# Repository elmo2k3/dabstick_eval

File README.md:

# DABStick Eval - Experimental board for SI4688 FM/DAB+ receiver with STM32F4 and audio codec

![Image of DABPStick Eval v1 PCB]
(https://github.com/elmo2k3/dabstick_eval/blob/master/pics/dabstick_v1.jpg)

## Warning

This project is still work in progress

## Hardware

* STM32F427VIT6 microcontroller
  * 2MB Flash, 256KB SRAM
  * Up to 180MHz, here 168MHz
* SI4688-A10-GM FM / HD / DAB / DAB + radio receiver
* CS43L22 Audio DAC with integrated class D speaker driver
* General purpose 2x40 pin headers
* Power by USB or screw connector

## Functional overview

![Graph of functional overview]
(https://github.com/elmo2k3/dabstick_eval/blob/master/doc/DABStick_overview.png)

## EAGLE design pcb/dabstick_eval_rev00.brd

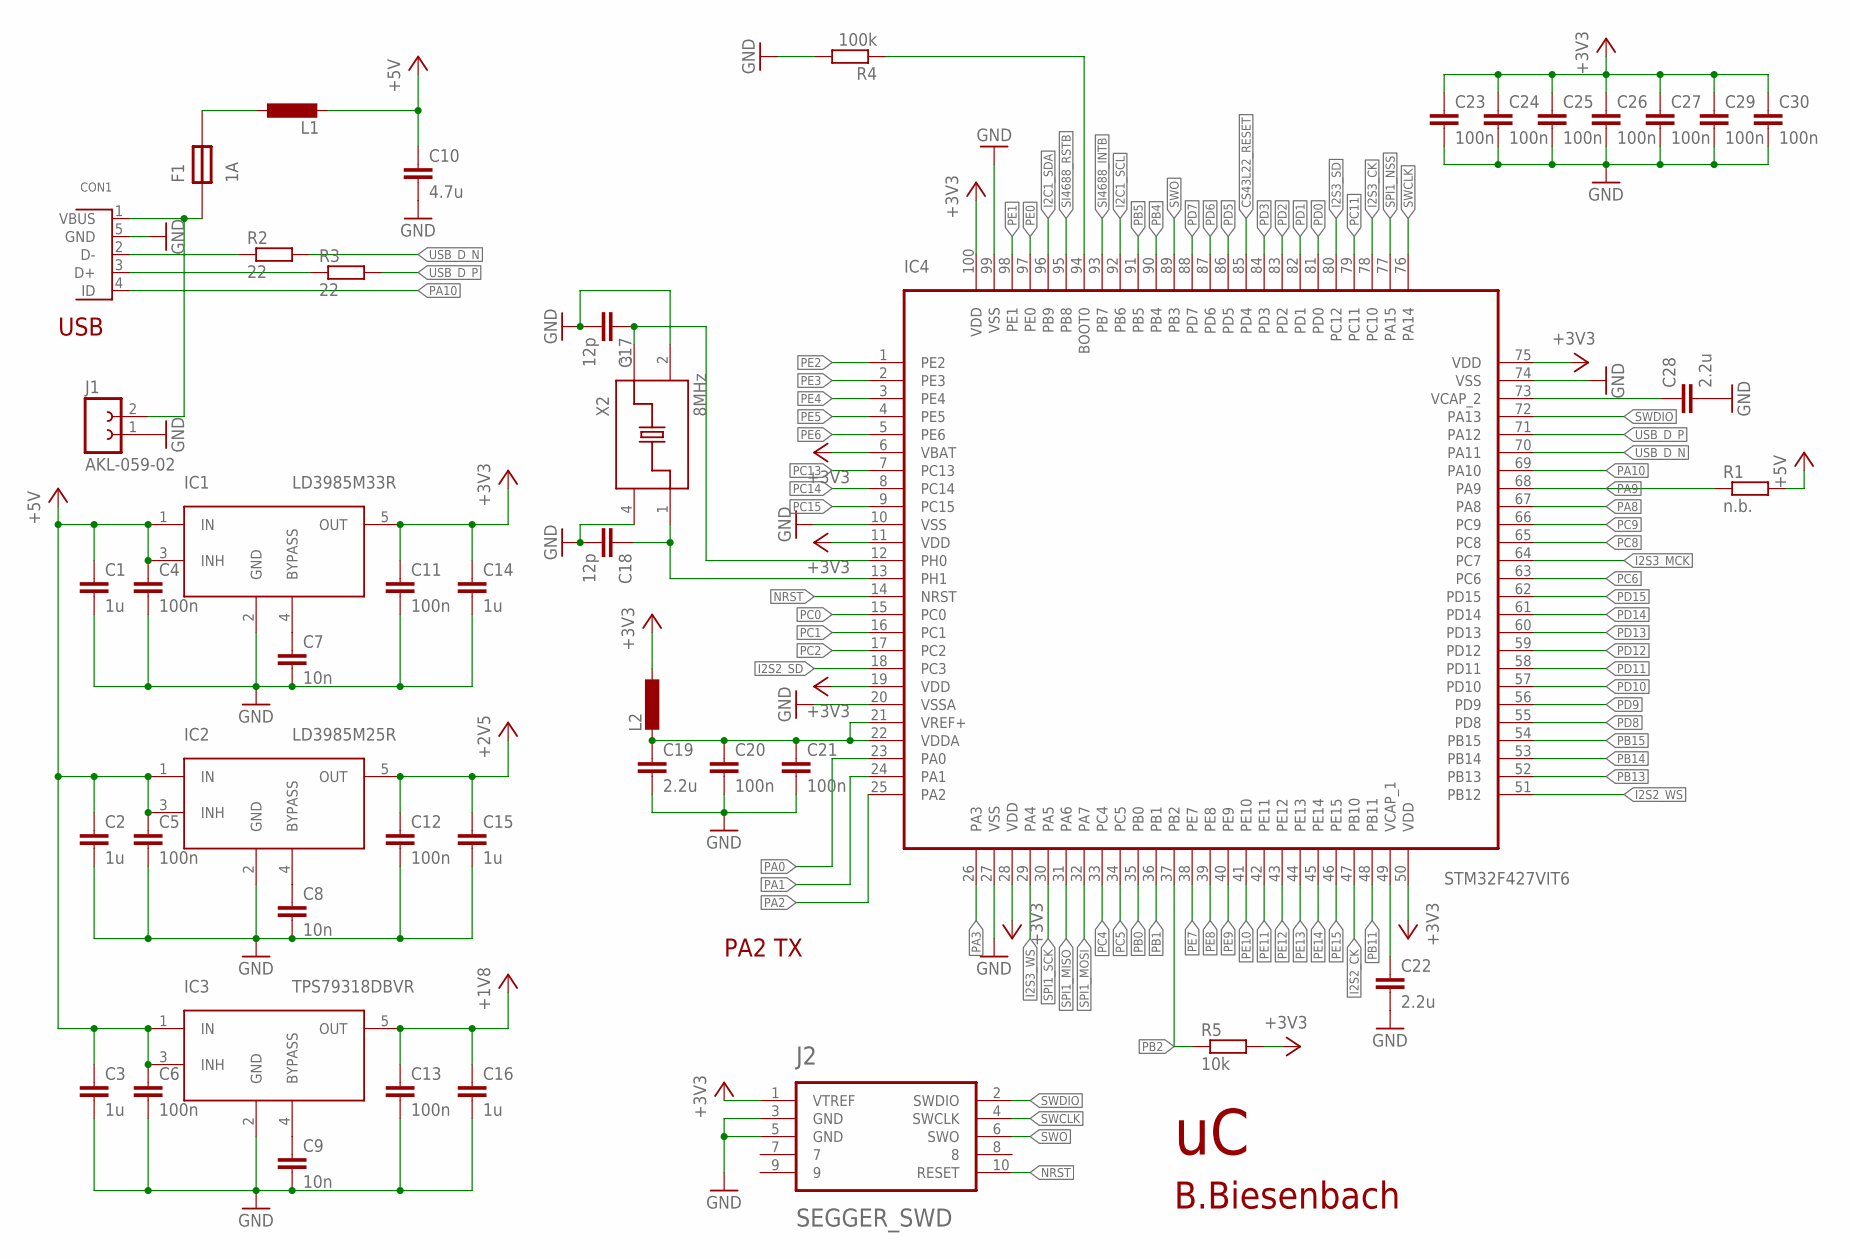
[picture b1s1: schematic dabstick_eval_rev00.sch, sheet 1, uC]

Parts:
C1, C2, C3, C14, C15, C16: 1u; SMD0603
C4, C5, C6, C11, C12, C13, C20, C21, C23, C24, C25, C26, C27, C29, C30: 100n; SMD0603
C7, C8, C9: 10n; SMD0603
C10: 4.7u; 0805
C17, C18: 12p; SMD0603
C19, C22, C28: 2.2u; SMD0603
CON1: USB; USB-B-MICRO-SMT
F1: 1A; SMD_FUSE
IC1: LD3985M33R; SOT23-5
IC2: LD3985M25R; SOT23-5
IC3: TPS79318DBVR; SOT23-5
IC4: STM32F427VIT6; LQFP100
J1: AKL-059-02
J2: SEGGER_SWD; HEADER_10_1.27
L1: L08050805; 0805
L2: L0603; SMD0603
R1: n.b.; SMD0603
R2, R3: 22; SMD0603
R4: 100k; SMD0603
R5: 10k; SMD0603
X2: 8MHz; XTAL_3.2X5

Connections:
+1V8: C13.1, C16.1, IC3.5 (OUT); also elsewhere on the board
+2V5: C12.1, C15.1, IC2.5 (OUT); also elsewhere on the board
+3V3: C11.1, C14.1, C23.1, C24.1, C25.1, C26.1, C27.1, C29.1, C30.1, IC1.5 (OUT), IC4.6 (VBAT), IC4.11 (VDD), IC4.19 (VDD), IC4.28 (VDD), IC4.50 (VDD), IC4.75 (VDD), IC4.100 (VDD), J2.1 (VTREF), L2.1, R5.2; also elsewhere on the board
+5V: C1.1, C2.1, C3.1, C4.1, C5.1, C6.1, C10.1, IC1.1 (IN), IC1.3 (INH), IC2.1 (IN), IC2.3 (INH), IC3.1 (IN), IC3.3 (INH), L1.2, R1.2; also elsewhere on the board
CS43L22_RESET: IC4.85 (PD4); also elsewhere on the board
GND: C1.2, C2.2, C3.2, C4.2, C5.2, C6.2, C7.2, C8.2, C9.2, C10.2, C11.2, C12.2, C13.2, C14.2, C15.2, C16.2, C17.2, C18.2, C19.2, C20.2, C21.2, C22.2, C23.2, C24.2, C25.2, C26.2, C27.2, C28.2, C29.2, C30.2, CON1.5 (GND), IC1.2 (GND), IC2.2 (GND), IC3.2 (GND), IC4.10 (VSS), IC4.20 (VSSA), IC4.27 (VSS), IC4.74 (VSS), IC4.99 (VSS), J1.1, J2.3 (GND), J2.5 (GND), R4.2, X2.2 (GND), X2.4 (GND); also elsewhere on the board
I2C1_SCL: IC4.92 (PB6); also elsewhere on the board
I2C1_SDA: IC4.96 (PB9); also elsewhere on the board
I2S2_CK: IC4.47 (PB10); also elsewhere on the board
I2S2_SD: IC4.18 (PC3); also elsewhere on the board
I2S2_WS: IC4.51 (PB12); also elsewhere on the board
I2S3_CK: IC4.78 (PC10); also elsewhere on the board
I2S3_MCK: IC4.64 (PC7); also elsewhere on the board
I2S3_SD: IC4.80 (PC12); also elsewhere on the board
I2S3_WS: IC4.29 (PA4); also elsewhere on the board
unnamed: C7.1, IC1.4 (BYPASS)
unnamed: C8.1, IC2.4 (BYPASS)
unnamed: C9.1, IC3.4 (BYPASS)
unnamed: C19.1, C20.1, C21.1, IC4.21 (VREF+), IC4.22 (VDDA), L2.2
unnamed: C28.1, IC4.73 (VCAP_2)
unnamed: C22.1, IC4.49 (VCAP_1)
unnamed: CON1.3 (D+), R3.1
unnamed: CON1.2 (D-), R2.1
unnamed: C18.1, IC4.13 (PH1), X2.1
unnamed: C17.1, IC4.12 (PH0), X2.3
unnamed: IC4.94 (BOOT0), R4.1
unnamed: F1.P$2, L1.1
unnamed: CON1.1 (VBUS), F1.P$1, J1.2
NRST: IC4.14 (NRST), J2.10 (RESET); also elsewhere on the board
PA0: IC4.23 (PA0); also elsewhere on the board
PA1: IC4.24 (PA1); also elsewhere on the board
PA2: IC4.25 (PA2); also elsewhere on the board
PA3: IC4.26 (PA3); also elsewhere on the board
PA8: IC4.67 (PA8); also elsewhere on the board
PA9: IC4.68 (PA9), R1.1; also elsewhere on the board
PA10: CON1.4 (ID), IC4.69 (PA10); also elsewhere on the board
PB0: IC4.35 (PB0); also elsewhere on the board
PB1: IC4.36 (PB1); also elsewhere on the board
PB2: IC4.37 (PB2), R5.1; also elsewhere on the board
PB4: IC4.90 (PB4); also elsewhere on the board
PB5: IC4.91 (PB5); also elsewhere on the board
PB11: IC4.48 (PB11); also elsewhere on the board
PB13: IC4.52 (PB13); also elsewhere on the board
PB14: IC4.53 (PB14); also elsewhere on the board
PB15: IC4.54 (PB15); also elsewhere on the board
PC0: IC4.15 (PC0); also elsewhere on the board
PC1: IC4.16 (PC1); also elsewhere on the board
PC2: IC4.17 (PC2); also elsewhere on the board
PC4: IC4.33 (PC4); also elsewhere on the board
PC5: IC4.34 (PC5); also elsewhere on the board
PC6: IC4.63 (PC6); also elsewhere on the board
PC8: IC4.65 (PC8); also elsewhere on the board
PC9: IC4.66 (PC9); also elsewhere on the board
PC11: IC4.79 (PC11); also elsewhere on the board
PC13: IC4.7 (PC13); also elsewhere on the board
PC14: IC4.8 (PC14); also elsewhere on the board
PC15: IC4.9 (PC15); also elsewhere on the board
PD0: IC4.81 (PD0); also elsewhere on the board
PD1: IC4.82 (PD1); also elsewhere on the board
PD2: IC4.83 (PD2); also elsewhere on the board
PD3: IC4.84 (PD3); also elsewhere on the board
PD5: IC4.86 (PD5); also elsewhere on the board
PD6: IC4.87 (PD6); also elsewhere on the board
PD7: IC4.88 (PD7); also elsewhere on the board
PD8: IC4.55 (PD8); also elsewhere on the board
PD9: IC4.56 (PD9); also elsewhere on the board
PD10: IC4.57 (PD10); also elsewhere on the board
PD11: IC4.58 (PD11); also elsewhere on the board
PD12: IC4.59 (PD12); also elsewhere on the board
PD13: IC4.60 (PD13); also elsewhere on the board
PD14: IC4.61 (PD14); also elsewhere on the board
PD15: IC4.62 (PD15); also elsewhere on the board
PE0: IC4.97 (PE0); also elsewhere on the board
PE1: IC4.98 (PE1); also elsewhere on the board
PE2: IC4.1 (PE2); also elsewhere on the board
PE3: IC4.2 (PE3); also elsewhere on the board
PE4: IC4.3 (PE4); also elsewhere on the board
PE5: IC4.4 (PE5); also elsewhere on the board
PE6: IC4.5 (PE6); also elsewhere on the board
PE7: IC4.38 (PE7); also elsewhere on the board
PE8: IC4.39 (PE8); also elsewhere on the board
PE9: IC4.40 (PE9); also elsewhere on the board
PE10: IC4.41 (PE10); also elsewhere on the board
PE11: IC4.42 (PE11); also elsewhere on the board
PE12: IC4.43 (PE12); also elsewhere on the board
PE13: IC4.44 (PE13); also elsewhere on the board
PE14: IC4.45 (PE14); also elsewhere on the board
PE15: IC4.46 (PE15); also elsewhere on the board
SI4688_INTB: IC4.93 (PB7); also elsewhere on the board
SI4688_RSTB: IC4.95 (PB8); also elsewhere on the board
SPI1_MISO: IC4.31 (PA6); also elsewhere on the board
SPI1_MOSI: IC4.32 (PA7); also elsewhere on the board
SPI1_NSS: IC4.77 (PA15); also elsewhere on the board
SPI1_SCK: IC4.30 (PA5); also elsewhere on the board
SWCLK: IC4.76 (PA14), J2.4 (SWCLK)
SWDIO: IC4.72 (PA13), J2.2 (SWDIO)
SWO: IC4.89 (PB3), J2.6 (SWO)
USB_D_N: IC4.70 (PA11), R2.2
USB_D_P: IC4.71 (PA12), R3.2

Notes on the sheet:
PA2 TX
B.Biesenbach

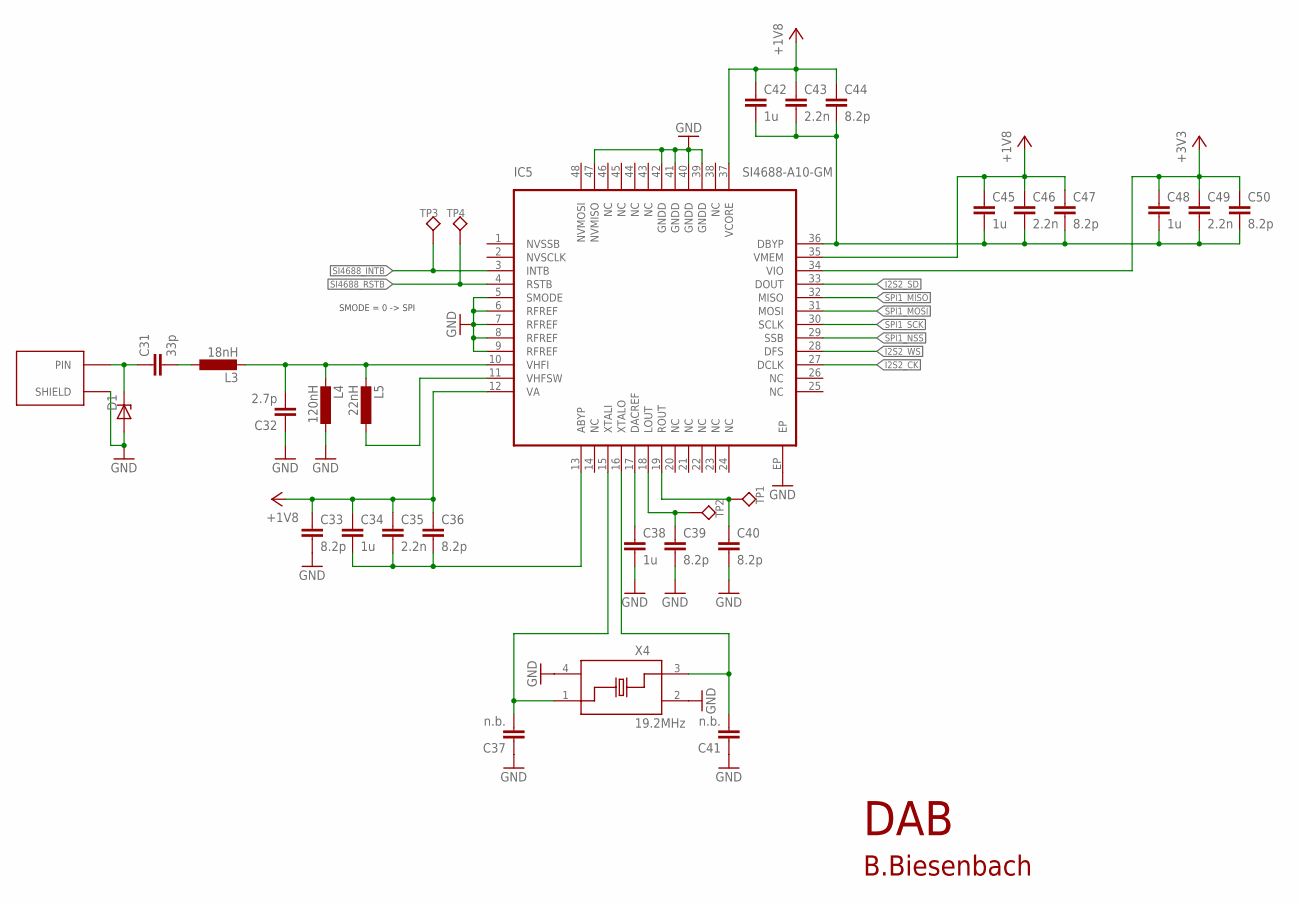
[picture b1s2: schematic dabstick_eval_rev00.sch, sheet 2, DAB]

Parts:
C31: 33p; SMD0402
C32: 2.7p; SMD0402
C33, C36, C39, C40, C44, C47, C50: 8.2p; SMD0603
C34, C38, C42, C45, C48: 1u; SMD0603
C35, C43, C46, C49: 2.2n; SMD0603
C37, C41: n.b.; SMD0402
D1: ESD9L5.0; SOD923
IC5: SI4688-A10-GM; QFN48
L3: 18nH; SMD0402
L4: 120nH; SMD0402
L5: 22nH; SMD0402
TP1, TP2: TP-2-MM
TP3, TP4: TP-1-MM
X3: SMA_LP_1.57MM
X4: 19.2MHz; XTAL_3.2X2.5

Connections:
+1V8: C33.1, C34.1, C35.1, C36.1, C42.1, C43.1, C44.1, C45.1, C46.1, C47.1, IC5.12 (VA), IC5.35 (VMEM), IC5.37 (VCORE); also elsewhere on the board
+3V3: C48.1, C49.1, C50.1, IC5.34 (VIO); also elsewhere on the board
GND: C32.1, C33.2, C37.1, C38.2, C39.2, C40.2, C41.1, D1.A, IC5.5 (SMODE), IC5.6 (RFREF), IC5.7 (RFREF), IC5.8 (RFREF), IC5.9 (RFREF), IC5.39 (GNDD), IC5.40 (GNDD), IC5.41 (GNDD), IC5.42 (GNDD), IC5.47 (NVMISO), IC5.EP, L4.1, X3.GND (SHIELD), X3.GND@1 (SHIELD), X3.GND@2 (SHIELD), X3.GND@3 (SHIELD), X4.2 (GND), X4.4 (GND); also elsewhere on the board
I2S2_CK: IC5.27 (DCLK); also elsewhere on the board
I2S2_SD: IC5.33 (DOUT); also elsewhere on the board
I2S2_WS: IC5.28 (DFS); also elsewhere on the board
unnamed: C31.2, L3.1
unnamed: C32.2, IC5.10 (VHFI), L3.2, L4.2, L5.2
unnamed: IC5.11 (VHFSW), L5.1
unnamed: C34.2, C35.2, C36.2, IC5.13 (ABYP)
unnamed: C42.2, C43.2, C44.2, C45.2, C46.2, C47.2, C48.2, C49.2, C50.2, IC5.36 (DBYP)
unnamed: C37.2, IC5.15 (XTALI), X4.1
unnamed: C41.2, IC5.16 (XTALO), X4.3
unnamed: C38.1, IC5.17 (DACREF)
RF_IN: C31.1, D1.K (C), X3.PIN
SI4688_INTB: IC5.3 (INTB), TP3.1; also elsewhere on the board
SI4688_LOUT: C39.1, IC5.18 (LOUT), TP2.P$1
SI4688_ROUT: C40.1, IC5.19 (ROUT), TP1.P$1
SI4688_RSTB: IC5.4 (RSTB), TP4.1; also elsewhere on the board
SPI1_MISO: IC5.32 (MISO); also elsewhere on the board
SPI1_MOSI: IC5.31 (MOSI); also elsewhere on the board
SPI1_NSS: IC5.29 (SSB); also elsewhere on the board
SPI1_SCK: IC5.30 (SCLK); also elsewhere on the board

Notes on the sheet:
DAB
SMODE = 0 -> SPI
B.Biesenbach

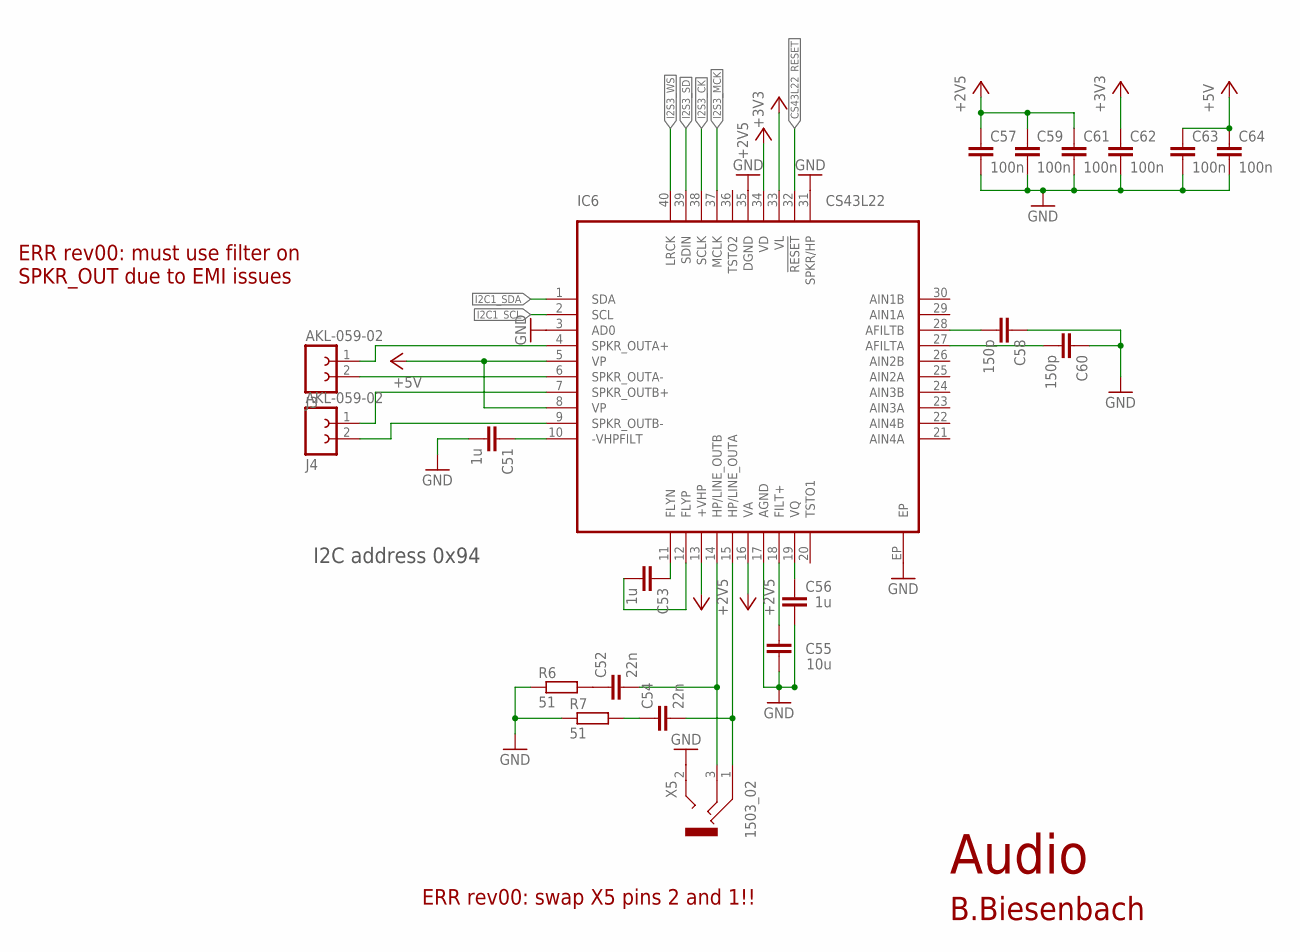
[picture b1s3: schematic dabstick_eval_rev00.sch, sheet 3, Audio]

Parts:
C51, C53, C56: 1u; SMD0603
C52, C54: 22n; SMD0603
C55: 10u; SMD0603
C57, C59, C61, C62, C63, C64: 100n; SMD0603
C58, C60: 150p; SMD0603
IC6: CS43L22; QFN40
J3, J4: AKL-059-02
R6, R7: 51; SMD0603
X5: 1503_02

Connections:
+2V5: C57.1, C59.1, C61.1, IC6.13 (+VHP), IC6.16 (VA), IC6.34 (VD); also elsewhere on the board
+3V3: C62.1, IC6.33 (VL); also elsewhere on the board
+5V: C63.1, C64.1, IC6.5 (VP), IC6.8 (VP); also elsewhere on the board
CS43L22_RESET: IC6.32 (!RESET); also elsewhere on the board
GND: C51.2, C55.1, C56.1, C57.2, C58.1, C59.2, C60.1, C61.2, C62.2, C63.2, C64.2, IC6.3 (AD0), IC6.17 (AGND), IC6.31 (SPKR/HP), IC6.35 (DGND), IC6.EP, R6.1, R7.1, X5.2; also elsewhere on the board
I2C1_SCL: IC6.2 (SCL); also elsewhere on the board
I2C1_SDA: IC6.1 (SDA); also elsewhere on the board
I2S3_CK: IC6.38 (SCLK); also elsewhere on the board
I2S3_MCK: IC6.37 (MCLK); also elsewhere on the board
I2S3_SD: IC6.39 (SDIN); also elsewhere on the board
I2S3_WS: IC6.40 (LRCK); also elsewhere on the board
unnamed: IC6.4 (SPKR_OUTA+), J3.1
unnamed: IC6.6 (SPKR_OUTA-), J3.2
unnamed: IC6.7 (SPKR_OUTB+), J4.1
unnamed: IC6.9 (SPKR_OUTB-), J4.2
unnamed: C54.2, IC6.15 (HP/LINE_OUTA), X5.1
unnamed: C52.2, IC6.14 (HP/LINE_OUTB), X5.3
unnamed: C52.1, R6.2
unnamed: C54.1, R7.2
unnamed: C56.2, IC6.19 (VQ)
unnamed: C55.2, IC6.18 (FILT+)
unnamed: C58.2, IC6.28 (AFILTB)
unnamed: C60.2, IC6.27 (AFILTA)
unnamed: C51.1, IC6.10 (-VHPFILT)
unnamed: C53.1, IC6.11 (FLYN)
unnamed: C53.2, IC6.12 (FLYP)

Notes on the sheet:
Audio
I2C address 0x94
B.Biesenbach
ERR rev00: swap X5 pins 2 and 1!!
ERR rev00: must use filter on SPKR_OUT due to EMI issues

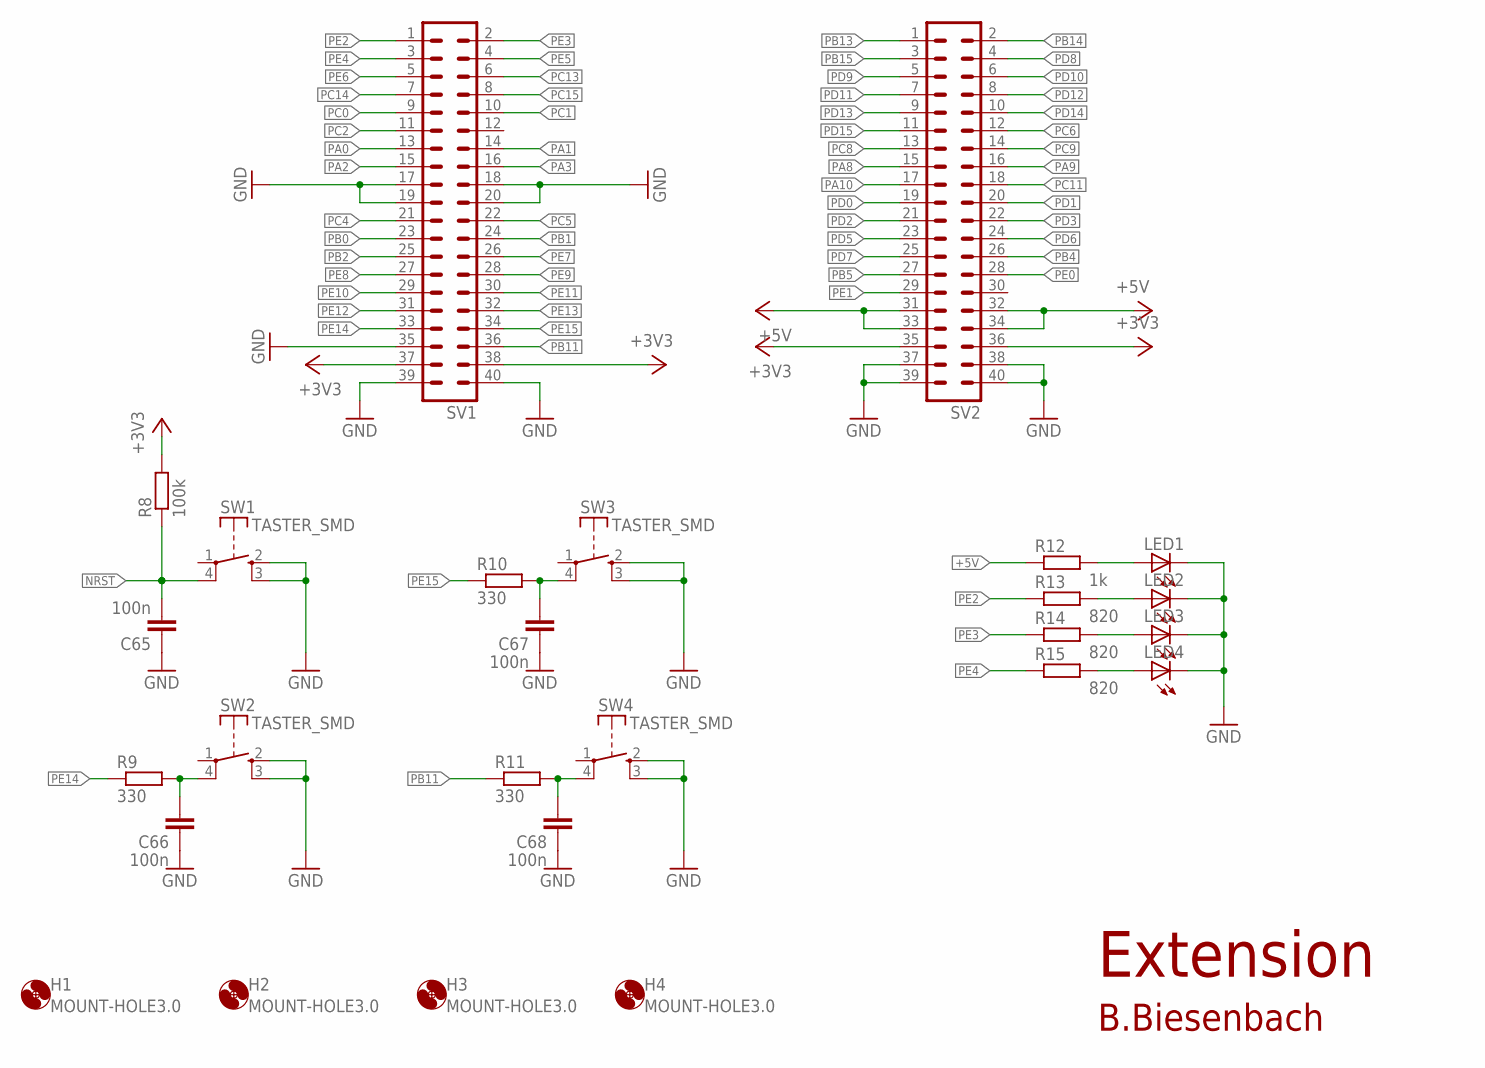
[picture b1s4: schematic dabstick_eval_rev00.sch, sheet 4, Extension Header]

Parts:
C65, C66, C67, C68: 100n; SMD0603
H1, H2, H3, H4: MOUNT-HOLE3.0; 3,0
LED1, LED2, LED3, LED4: LEDCHIPLED_0603; CHIPLED_0603
R8: 100k; SMD0603
R9, R10, R11: 330; SMD0603
R12: 1k; SMD0603
R13, R14, R15: 820; SMD0603
SV1, SV2: MA20-2
SW1, SW2, SW3, SW4: TASTER_SMD; TASTER_SMD_ALPS

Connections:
+3V3: R8.2, SV1.37, SV1.38, SV2.35, SV2.36; also elsewhere on the board
+5V: R12.1, SV2.31, SV2.32, SV2.33, SV2.34; also elsewhere on the board
GND: C65.1, C66.1, C67.1, C68.1, LED1.C, LED2.C, LED3.C, LED4.C, SV1.17, SV1.18, SV1.19, SV1.20, SV1.35, SV1.39, SV1.40, SV2.37, SV2.38, SV2.39, SV2.40, SW1.2 (S), SW1.3 (S), SW2.2 (S), SW2.3 (S), SW3.2 (S), SW3.3 (S), SW4.2 (S), SW4.3 (S); also elsewhere on the board
unnamed: C66.2, R9.2, SW2.4
unnamed: C68.2, R11.2, SW4.4
unnamed: C67.2, R10.2, SW3.4
unnamed: LED1.A, R12.2
unnamed: LED2.A, R13.2
unnamed: LED3.A, R14.2
unnamed: LED4.A, R15.2
NRST: C65.2, R8.1, SW1.4; also elsewhere on the board
PA0: SV1.13; also elsewhere on the board
PA1: SV1.14; also elsewhere on the board
PA2: SV1.15; also elsewhere on the board
PA3: SV1.16; also elsewhere on the board
PA8: SV2.15; also elsewhere on the board
PA9: SV2.16; also elsewhere on the board
PA10: SV2.17; also elsewhere on the board
PB0: SV1.23; also elsewhere on the board
PB1: SV1.24; also elsewhere on the board
PB2: SV1.25; also elsewhere on the board
PB4: SV2.26; also elsewhere on the board
PB5: SV2.27; also elsewhere on the board
PB11: R11.1, SV1.36; also elsewhere on the board
PB13: SV2.1; also elsewhere on the board
PB14: SV2.2; also elsewhere on the board
PB15: SV2.3; also elsewhere on the board
PC0: SV1.9; also elsewhere on the board
PC1: SV1.10; also elsewhere on the board
PC2: SV1.11; also elsewhere on the board
PC4: SV1.21; also elsewhere on the board
PC5: SV1.22; also elsewhere on the board
PC6: SV2.12; also elsewhere on the board
PC8: SV2.13; also elsewhere on the board
PC9: SV2.14; also elsewhere on the board
PC11: SV2.18; also elsewhere on the board
PC13: SV1.6; also elsewhere on the board
PC14: SV1.7; also elsewhere on the board
PC15: SV1.8; also elsewhere on the board
PD0: SV2.19; also elsewhere on the board
PD1: SV2.20; also elsewhere on the board
PD2: SV2.21; also elsewhere on the board
PD3: SV2.22; also elsewhere on the board
PD5: SV2.23; also elsewhere on the board
PD6: SV2.24; also elsewhere on the board
PD7: SV2.25; also elsewhere on the board
PD8: SV2.4; also elsewhere on the board
PD9: SV2.5; also elsewhere on the board
PD10: SV2.6; also elsewhere on the board
PD11: SV2.7; also elsewhere on the board
PD12: SV2.8; also elsewhere on the board
PD13: SV2.9; also elsewhere on the board
PD14: SV2.10; also elsewhere on the board
PD15: SV2.11; also elsewhere on the board
PE0: SV2.28; also elsewhere on the board
PE1: SV2.29; also elsewhere on the board
PE2: R13.1, SV1.1; also elsewhere on the board
PE3: R14.1, SV1.2; also elsewhere on the board
PE4: R15.1, SV1.3; also elsewhere on the board
PE5: SV1.4; also elsewhere on the board
PE6: SV1.5; also elsewhere on the board
PE7: SV1.26; also elsewhere on the board
PE8: SV1.27; also elsewhere on the board
PE9: SV1.28; also elsewhere on the board
PE10: SV1.29; also elsewhere on the board
PE11: SV1.30; also elsewhere on the board
PE12: SV1.31; also elsewhere on the board
PE13: SV1.32; also elsewhere on the board
PE14: R9.1, SV1.33; also elsewhere on the board
PE15: R10.1, SV1.34; also elsewhere on the board

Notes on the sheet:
Extension
B.Biesenbach

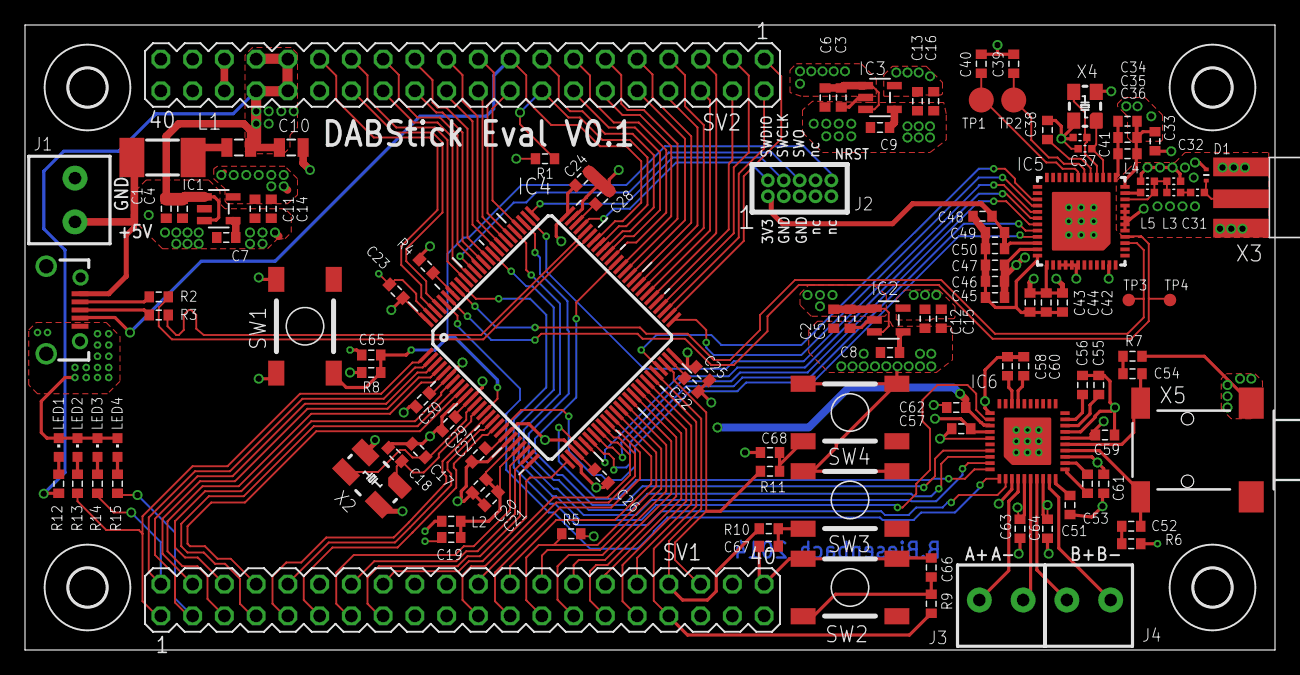
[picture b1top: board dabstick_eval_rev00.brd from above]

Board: 4 copper layers, 100.0 x 50.0 mm, 123 parts (0 on the bottom side), 132 nets.

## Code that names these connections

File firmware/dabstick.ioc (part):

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Mcu.Name=STM32F427V(G-I)Tx
Mcu.Package=LQFP100
Mcu.UserName=STM32F427VITx
PA11.Mode=Device_Only
PA11.Signal=USB_OTG_FS_DM
PA12.Mode=Device_Only
PA12.Signal=USB_OTG_FS_DP
PA13.Mode=Trace-Asynchronous_SW
PA13.Signal=SYS_JTMS-SWDIO
PA14.Mode=Trace-Asynchronous_SW
PA14.Signal=SYS_JTCK-SWCLK
PA15.GPIOParameters=GPIO_ModeDefaultOutputPP,GPIO_Label,GPIO_Speed,GPIO_PuPd
PA15.GPIO_Label=SI46XX_NSS
PA15.GPIO_ModeDefaultOutputPP=GPIO_MODE_OUTPUT_PP
PA15.GPIO_PuPd=GPIO_NOPULL
PA15.GPIO_Speed=GPIO_SPEED_LOW
PA15.Signal=GPIO_Output
PA2.Mode=Asynchronous
PA2.Signal=USART2_TX
PA3.GPIOParameters=GPIO_Speed,GPIO_PuPd,GPIO_Mode
PA3.GPIO_Mode=GPIO_MODE_AF_PP
PA3.GPIO_PuPd=GPIO_PULLDOWN
PA3.GPIO_Speed=GPIO_SPEED_LOW
PA3.Mode=Asynchronous
PA3.Signal=USART2_RX
PA4.Mode=Half_Duplex_Master
PA4.Signal=I2S3_WS
PA5.Mode=Full_Duplex_Master
PA5.Signal=SPI1_SCK
PA6.Mode=Full_Duplex_Master
PA6.Signal=SPI1_MISO
PA7.Mode=Full_Duplex_Master
PA7.Signal=SPI1_MOSI
PB0.GPIOParameters=GPIO_Label,GPIO_PuPd,GPIO_Mode
PB0.GPIO_Label=ROT_BT
PB0.GPIO_Mode=GPIO_MODE_INPUT
PB0.GPIO_PuPd=GPIO_PULLUP
PB0.Signal=GPIO_Input
PB1.Signal=S_TIM3_CH4
PB10.Mode=Half_Duplex_Master
PB10.Signal=I2S2_CK
PB11.GPIOParameters=GPIO_Label,GPIO_PuPd,GPIO_Mode
PB11.GPIO_Label=SW4
PB11.GPIO_Mode=GPIO_MODE_INPUT
PB11.GPIO_PuPd=GPIO_PULLUP
PB11.Signal=GPIO_Input
PB12.Mode=Half_Duplex_Master
PB12.Signal=I2S2_WS
PB13.Signal=GPIO_Output
PB14.Signal=GPIO_Output
PB2/BOOT1.GPIOParameters=GPIO_PuPd,GPIO_Mode
PB2/BOOT1.GPIO_Mode=GPIO_MODE_INPUT
PB2/BOOT1.GPIO_PuPd=GPIO_PULLUP
PB2/BOOT1.Signal=GPIO_Input
PB3.Mode=Trace-Asynchronous_SW
PB3.Signal=SYS_JTDO-SWO
PB6.GPIOParameters=GPIO_Speed,GPIO_PuPd,GPIO_Mode
PB6.GPIO_Mode=GPIO_MODE_AF_OD
PB6.GPIO_PuPd=GPIO_PULLUP
PB6.GPIO_Speed=GPIO_SPEED_LOW
PB6.Mode=I2C
PB6.Signal=I2C1_SCL
PB7.GPIOParameters=GPIO_Label,GPIO_PuPd,GPIO_Mode
PB7.GPIO_Label=SI4688_INTB
PB7.GPIO_Mode=GPIO_MODE_INPUT
PB7.GPIO_PuPd=GPIO_PULLUP
PB7.Signal=GPIO_Input
PB8.GPIOParameters=GPIO_Label,GPIO_ModeDefaultOutputPP,GPIO_Speed,GPIO_PuPd
PB8.GPIO_Label=SI4688_RSTB
PB8.GPIO_ModeDefaultOutputPP=GPIO_MODE_OUTPUT_PP
PB8.GPIO_PuPd=GPIO_NOPULL
PB8.GPIO_Speed=GPIO_SPEED_LOW
PB8.Signal=GPIO_Output
PB9.GPIOParameters=GPIO_Speed,GPIO_PuPd,GPIO_Mode
PB9.GPIO_Mode=GPIO_MODE_AF_OD
PB9.GPIO_PuPd=GPIO_PULLUP
PB9.GPIO_Speed=GPIO_SPEED_LOW
PB9.Mode=I2C
PB9.Signal=I2C1_SDA
PC10.Mode=Half_Duplex_Master
PC10.Signal=I2S3_CK
PC12.Mode=Half_Duplex_Master
PC12.Signal=I2S3_SD
PC13.GPIOParameters=GPIO_Label,GPIO_ModeDefaultOutputPP,GPIO_Speed,GPIO_PuPd
PC13.GPIO_Label=LCD_CS
PC13.GPIO_ModeDefaultOutputPP=GPIO_MODE_OUTPUT_PP
PC13.GPIO_PuPd=GPIO_NOPULL
PC13.GPIO_Speed=GPIO_SPEED_LOW
PC13.Signal=GPIO_Output
PC14/OSC32_IN.GPIOParameters=GPIO_Label,GPIO_ModeDefaultOutputPP,GPIO_Speed,GPIO_PuPd
PC14/OSC32_IN.GPIO_Label=LCD_RES
PC14/OSC32_IN.GPIO_ModeDefaultOutputPP=GPIO_MODE_OUTPUT_PP
PC14/OSC32_IN.GPIO_PuPd=GPIO_NOPULL
PC14/OSC32_IN.GPIO_Speed=GPIO_SPEED_LOW
PC14/OSC32_IN.Signal=GPIO_Output
PC15/OSC32_OUT.GPIOParameters=GPIO_Label,GPIO_ModeDefaultOutputPP,GPIO_Speed,GPIO_PuPd
PC15/OSC32_OUT.GPIO_Label=LCD_CD
PC15/OSC32_OUT.GPIO_ModeDefaultOutputPP=GPIO_MODE_OUTPUT_PP
PC15/OSC32_OUT.GPIO_PuPd=GPIO_NOPULL
PC15/OSC32_OUT.GPIO_Speed=GPIO_SPEED_LOW
PC15/OSC32_OUT.Signal=GPIO_Output
PC3.Mode=Half_Duplex_Master
PC3.Signal=I2S2_SD
PC4.GPIOParameters=GPIO_Label,GPIO_PuPd,GPIO_Mode
PC4.GPIO_Label=ROT_A
PC4.GPIO_Mode=GPIO_MODE_INPUT
PC4.GPIO_PuPd=GPIO_PULLUP
PC4.Signal=GPIO_Input
PC5.GPIOParameters=GPIO_Label,GPIO_PuPd,GPIO_Mode
PC5.GPIO_Label=ROT_B
PC5.GPIO_Mode=GPIO_MODE_INPUT
PC5.GPIO_PuPd=GPIO_PULLUP
PC5.Signal=GPIO_Input
PC6.Mode=Master_Clock_Activated
PC6.Signal=I2S2_MCK
PC7.GPIOParameters=GPIO_Speed,GPIO_PuPd,GPIO_Mode
PC7.GPIO_Mode=GPIO_MODE_AF_PP
PC7.GPIO_PuPd=GPIO_NOPULL
PC7.GPIO_Speed=GPIO_SPEED_FAST
PC7.Mode=Master_Clock_Activated
PC7.Signal=I2S3_MCK
PD4.GPIOParameters=GPIO_Label,GPIO_ModeDefaultOutputPP,GPIO_Speed,GPIO_PuPd
PD4.GPIO_Label=CS43L22_RESET
PD4.GPIO_ModeDefaultOutputPP=GPIO_MODE_OUTPUT_PP
PD4.GPIO_PuPd=GPIO_NOPULL
PD4.GPIO_Speed=GPIO_SPEED_LOW
PD4.Signal=GPIO_Output
PE12.Mode=TX_Only_Simplex_Unidirect_Master
PE12.Signal=SPI4_SCK
PE14.GPIOParameters=GPIO_Label,GPIO_PuPd,GPIO_Mode
PE14.GPIO_Label=SW2
PE14.GPIO_Mode=GPIO_MODE_INPUT
PE14.GPIO_PuPd=GPIO_PULLUP
PE14.Signal=GPIO_Input
PE15.GPIOParameters=GPIO_Label,GPIO_PuPd,GPIO_Mode
PE15.GPIO_Label=SW3
PE15.GPIO_Mode=GPIO_MODE_INPUT
PE15.GPIO_PuPd=GPIO_PULLUP
PE15.Signal=GPIO_Input
PE2.GPIOParameters=GPIO_Label,GPIO_ModeDefaultOutputPP,GPIO_Speed,GPIO_PuPd
PE2.GPIO_Label=LED1
PE2.GPIO_ModeDefaultOutputPP=GPIO_MODE_OUTPUT_PP
PE2.GPIO_PuPd=GPIO_NOPULL
PE2.GPIO_Speed=GPIO_SPEED_LOW
PE2.Signal=GPIO_Output
PE3.GPIOParameters=GPIO_Label,GPIO_ModeDefaultOutputPP,GPIO_Speed,GPIO_PuPd
PE3.GPIO_Label=LED2
PE3.GPIO_ModeDefaultOutputPP=GPIO_MODE_OUTPUT_PP
PE3.GPIO_PuPd=GPIO_NOPULL
PE3.GPIO_Speed=GPIO_SPEED_LOW
PE3.Signal=GPIO_Output
PE4.GPIOParameters=GPIO_Label,GPIO_ModeDefaultOutputPP,GPIO_Speed,GPIO_PuPd
PE4.GPIO_Label=LED3
PE4.GPIO_ModeDefaultOutputPP=GPIO_MODE_OUTPUT_PP
PE4.GPIO_PuPd=GPIO_NOPULL
PE4.GPIO_Speed=GPIO_SPEED_LOW
PE4.Signal=GPIO_Output
PE6.Mode=TX_Only_Simplex_Unidirect_Master
PE6.Signal=SPI4_MOSI
PE7.GPIOParameters=GPIO_PuPd,GPIO_Mode
PE7.GPIO_Mode=GPIO_MODE_INPUT
PE7.GPIO_PuPd=GPIO_PULLUP
PE7.Signal=GPIO_Input
PH0/OSC_IN.Mode=HSE-External-Oscillator
PH0/OSC_IN.Signal=RCC_OSC_IN
PH1/OSC_OUT.Mode=HSE-External-Oscillator
PH1/OSC_OUT.Signal=RCC_OSC_OUT
RCC.HSE_VALUE=8000000
RCC.SYSCLKSource=RCC_SYSCLKSOURCE_PLLCLK

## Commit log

2014-11-26 some more info in readme
2014-12-21 bom added
